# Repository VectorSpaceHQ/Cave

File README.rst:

An open source, low-cost, Raspberry Pi powered, smart thermostat. Caves are generally cooler than nests.

Overview
=======
This program's goal is to maximize the amount of time spent in the comfort zone while minimizing the energy spent when the building is occupied.

Structure
========
This system is composed of a server, one or more thermostats, and optional nodes. Their purposes and interactions are as follows,

Server
-------
The server hosts the MySQL database and the web interface. Its purpose is to collect and analyze the sensor data from the thermostat(s) and any additional nodes, and use that information to direct the thermostat(s). In essence, the server is smart. The server can be a dedicated computer or it can run on the Raspberry Pi, alongside the thermostat program.

Thermostat
-------------
The thermostat measures temperature and directly interfaces with the wiring of the HVAC unit. It reports all measurements to the server and its actions are determined by the server. The thermostat is intended to be the Raspberry Pi.

Nodes
------
Nodes are optional pieces of hardware that provide additional sensor data to the MySQL database such as temperatures, humidity, and motion. Nodes might be of value in large spaces or in rooms isolated from the thermostat.

Nodes publish data using the MQTT protocol. This is done rather than modifying the MySQL database directly, simply because these nodes are small and rarely support SQL, as in the case of the ESP8266. The RPi subscribes to the MQTT channel and inserts the data it receives into the SQL database.

Installation
===========
clone the repository to the server and thermostat(s).
::
   git clone https://github.com/VectorSpaceHQ/Cave

Server
-------
Install mysql server on the server.
::
   sudo apt-get install mysql-server

Install supporting packages.
::
   sudo apt-get install python3-dev python3-pip python3-setuptools libmysqlclient-dev python3-mysql

Generate the initial MySQL database manually, then run ./src/database.py to create the tables
::
   mysql
   CREATE DATABASE hvac;
   quit
   ./src/database.py

You can confirm that the hvac database was added to your mysql server, by loging in at http://localhost/phpmyadmin/

Install required python packages.
::
   sudo pip3 install -r ./src/requirements.txt

Install Mosquitto on the server for MQTT brokering.
::
   sudo apt-get install mosquitto

Modify server/token.txt and server/server.conf files with appropriate values based on your wiring and preferences.

Thermostat
-----------
Install required python packages.
::
   sudo pip3 install -r ./thermostat/requirements.txt

Modify thermostat/token.txt and thermostat/thermostat.conf files with appropriate values based on your wiring and preferences.

Enable SPI and 1-Wire.
::
   sudo raspi-config
> Advanced Options > Enable SPI and 1-Wire

Services
copy cave_server.service to /etc/systemd/system/ on the server
copy cave_thermostat.service to /etc/systemd/system/ on the thermostat (RPi)

enable both of these services on their respective machines using
sudo systemctl enable cave_server.service
sudo systemctl enable cave_thermostat.service

Usage
=====
On the server,
::
   ./server/server.py start

On the RPi thermostat run,
::
   ./thermostat/thermostat.py start

MySQL database
=============
The database contains four tables.

ModuleInfo
-----------
This table contains an entry for each module (thermostat or node) connected to the system. It includes a unique ID, a description of the module's location, a firmware version, and boolean values to represent the presence of temperature, humidity, light, and motion sensors.

SensorData
-------------
This table logs all of the sensor readings, including the thermostat(s).

readingID, time, moduleID, location, temperature, humidity, light, sound, motion

ThermostatLog
-----------------
This table logs only the thermostat readings.

timeStamp, mode, moduleID, MinTemp, MaxTemp, actualTemp, coolOn, heatOn, fanOn, auxOn

ThermostatSet
----------------
This table provides the current directive for the thermostat(s). The server writes to this table and the thermostat reads from it.

timeStamp, moduleID, targetTemp, targetMode, expiryTime, entryNo

SystemLog
-----------
This table logs the state of the entire system.
timeStamp, Tthermostat, Toutside, Ttarget, Poccupancy

Testing
======
This software can be tested entirely on a single Raspberry Pi. Install the sample database found in /test, then run both the server.py and thermostat.py programs.
::
    mysql -uroot -p hvac < ./test/hvac_data.txt

    python3 -m unittest discover

Hardware
=======
Below is a wiring diagram for a Raspberry Pi zero with a temperature sensor, PIR sensor, and 4 channel relay.

.. image:: ext/thermostat_schematic_bb.png
           :align: center

** Standard thermostat pins
*** Honeywell TH6320U2008
pin spacing of 5mm (https://www.mouser.com/ProductDetail/845-30.359), 1.3mm diameter. two 8 pin columns separated by 44.4mm (1.75in)
*** Honeywell TH5320U1001
pin spacing of 5mm (https://www.mouser.com/ProductDetail/845-30.359), 1.3mm diameter. One 9 pin column.

HVAC 101
=======
The following HVAC information is coppied directly from, https://github.com/Willseph/RaspberryPiThermostat

HVAC 101

HVAC (heating, ventilating, and air conditioning) can be implemented in different ways within a house or apartment, and varies for different countries based on the wiring and such. I'm not an expert in HVAC systems, I pretty much just learned enough to get by for this project, but here's a pretty useful guide: https://lrak.net/wiki/Thermostat_signals_and_wiring.html

My particular apartment uses a heat pump, which uses the very same compressor action for the air conditioner. The only difference is the air flow. This makes it possible to, in my case, use four wires from the HVAC panel behind the original thermostat for this project:

R (Red): This is the "common" wire, meaning that a circuit is completed when any of the other wires are connected to this one, hence the relay module.
G (Green): This is the signal for the fan, which becomes activated when connected to R.
Y (Yellow): This is the signal for the compressor. By default, the air flow is set to blow heat into the apartment.
O (Orange): This is the signal to reverse the air flow from the compressor. With Y and O both active, the flow changes to blow cool air into the apartment.
I broke this down to a pretty simple formula while I started writing the software for the controller:

R + G = Fan
R + G + Y = Heater
R + G + Y + O = Air conditioner

It's also very important to note that the wires coming out of my HVAC use a low voltage at 24V, not mains power. With a relay module completing the circuits, it should still work with mains electricity, but it is very dangerous and you should NOT mess with mains power unless you know exactly what you're doing! An accident involving high voltage and current can very easily kill you.

If your home HVAC does not use a compressor heat pump or for another reason you cannot use the same setup I'm using, you will have to do some research and potentially adjust the hvaccontroller.py script accordingly.

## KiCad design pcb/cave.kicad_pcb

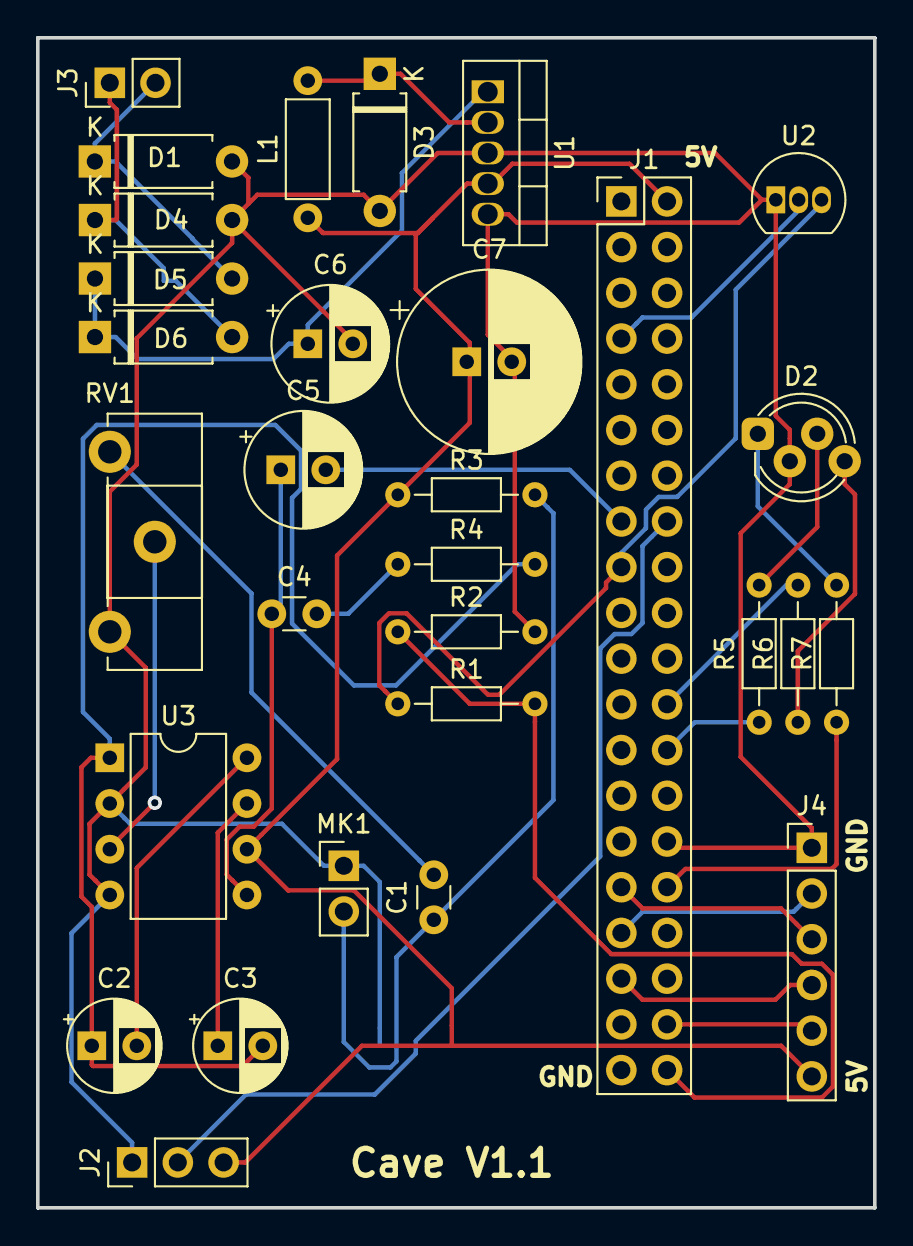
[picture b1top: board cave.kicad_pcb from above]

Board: 2 copper layers, 46.5 x 65.0 mm, 30 parts (0 on the bottom side), 29 nets.

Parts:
C1: 0.1uF; C_Disc_D3.0mm_W1.6mm_P2.50mm
C2, C3: 10uF; CP_Radial_D5.0mm_P2.50mm
C4: 0.047uF; C_Disc_D3.0mm_W1.6mm_P2.50mm
C5, C6: 100uF; CP_Radial_D6.3mm_P2.50mm
C7: 1000uF; CP_Radial_D10.0mm_P2.50mm
D1, D4, D5, D6: D_Small; D_A-405_P7.62mm_Horizontal
D2: LED_RCBG; LED_D5.0mm-4_RGB_Staggered_Pins
D3: D_Schottky; D_A-405_P7.62mm_Horizontal
J1: Raspberry_Pi_2_3; PinHeader_2x20_P2.54mm_Vertical
J2: PIRsensor; PinHeader_1x03_P2.54mm_Vertical
J3: PWR; PinHeader_1x02_P2.54mm_Vertical
J4: RelayOutput; PinHeader_1x06_P2.54mm_Vertical
L1: 100uH; L_Axial_L5.3mm_D2.2mm_P7.62mm_Horizontal_Vishay_IM-1
MK1: Microphone; PinHeader_1x02_P2.54mm_Vertical
R1: R_PHOTO; R_Axial_DIN0204_L3.6mm_D1.6mm_P7.62mm_Horizontal
R2: 10K; R_Axial_DIN0204_L3.6mm_D1.6mm_P7.62mm_Horizontal
R3: 1K; R_Axial_DIN0204_L3.6mm_D1.6mm_P7.62mm_Horizontal
R4: 10; R_Axial_DIN0204_L3.6mm_D1.6mm_P7.62mm_Horizontal
R5, R6, R7: 220; R_Axial_DIN0204_L3.6mm_D1.6mm_P7.62mm_Horizontal
RV1: 10K; Potentiometer_ACP_CA14-H2,5_Horizontal
U1: LM2576S-5; TO-220-5_Vertical
U2: DS18B20; TO-92_Inline
U3: LM386; DIP-8_W7.62mm

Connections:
+3V3: J1.17, R1.1, U2.3
+5V: C7.1, J1.2, J2.3, J4.6, L1.1, R3.1, U1.4, U3.6
+24V: D1.1, D5.2, J3.2
-24V: D4.1, D6.2, J3.1
/MicInput: C5.2, J1.15
/PIR: J1.16, J2.2
GND: C6.2, C7.2, D1.2, D2.2, D3.2, D4.2, J1.30, J2.1, J4.1, MK1.1, R2.2, RV1.3, U1.3, U1.5, U2.1, U3.2, U3.4
unnamed: C1.1, MK1.2, R3.2
unnamed: C1.2, RV1.1
unnamed: C2.1, C3.2, R4.2, U3.1
unnamed: C2.2, U3.8
unnamed: C3.1, U3.7
unnamed: C4.1, C5.1, U3.5
unnamed: C4.2, R4.1
unnamed: C6.1, D5.1, D6.1, U1.1
unnamed: D2.1, R7.2
unnamed: D2.3, R5.2
unnamed: D2.4, R6.1
unnamed: D3.1, L1.2, U1.2
unnamed: J1.7, U2.2
unnamed: J1.24, R6.2
unnamed: J1.26, R5.1
unnamed: J1.31, J4.3
unnamed: J1.32, R7.1
unnamed: J1.33, J4.2
unnamed: J1.35, J4.4
unnamed: J1.38, J4.5
unnamed: J1.40, R1.2, R2.1
unnamed: RV1.2, U3.3

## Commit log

2017-08-14 Initial commit. Nonworking state
2017-08-14 Removed developing feature
2017-08-14 corrected config file name
2017-08-14 Added config files. Still missing credentials
2017-08-14 py2to3
2017-08-14 added more sql detail to readme
2017-08-14 trying to figure out ReST
2017-08-15 expanded pyowm. Corrected logic in main loop
2017-08-15 Added occupancy check
2017-08-15 assume unoccupied before checking data
2017-08-15 Limit the sensor data query to last 50 entries
2017-08-15 fixed sorting of sensor data query
2017-08-15 some work on occupancy prediction. Still work to do
2017-08-15 py2to3 on thermostat code
2017-08-15 rename main files
2017-08-15 logging added to thermostat.py
2017-08-15 cleaning up thermostat.py
2017-08-18 minor changes
2017-08-25 Installed package on pi. updated documentation on installation and usage
2017-08-25 Updated thermostat.conf to reflect my test setup
2017-08-25 Added thermostat token file
2017-08-25 adding initialization functions to populate DB
2017-08-26 readme updates
2017-08-26 initialization functions working
2017-08-26 removed unused tables from sql schema
2017-08-26 cleanup of .sql inital database
2017-08-26 removed fan actuation from idle mode. Needs to be smarter
2017-08-26 added weather back in. Fixed sort order of sensor data
2017-08-27 changed comfort zone for easier testing
2017-08-27 idle was missing when outside temp is in comfort zone
2017-08-27 Added motion detection support
2017-08-27 Cleaned up getTemp function. Removed database communication
2017-08-28 began heat rate calculation
2017-08-29 sloppy but working implementation of an esp node
2017-08-29 began adding mqtt to server
2017-08-29 moved todo items into TODO file
2017-08-29 updates to TODO list
2017-08-29 added code support to .rst
2017-08-29 testing code support
2017-08-29 starting to understand rst syntax
2017-08-29 rst cleanup
2017-08-29 Reorg installation instructions
2017-08-29 Reorg rst
2017-08-29 Removed warranty statement from README since license covers it better
2017-08-30 Fix server install instructions
2017-08-30 Add python3-pip to the supporting packages
2017-08-30 Add python3-setuptools to the supporting packages
2017-08-30 added ping.lua to send data via GET request
2017-08-30 Add test data
2017-08-30 beginning of an error handler for the thermostat
2017-08-31 Added check_temp func to error.py. Removed Nooganeer's routes.py
2017-09-02 Initial module testing.
2017-09-02 Fixed syntax error.
2017-09-02 Fixed another syntax error.
2017-09-02 Minor testing changes.
2017-09-05 initial commit of wiring schematic
2017-09-05 Remove TODO file. Switched to github's issues
2017-09-05 added some pseudocode for email notification
2017-09-05 incorporating use of error checking
2017-09-05 Changed sensordata entry from 'occupied' to 'motion'. Sensor shouldn't be smart enough to determine if space is occupied. It detects motion. Let the server determine whether the space is occupied bas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
2017-09-05 added analysis.py file
2017-09-11 minor changes to get code running
2017-09-11 commented some weather code to get things running
2017-09-11 RGBled working
2017-09-22 Refactored server.py, moving logic from the run function into separate functions. Hopefully making code more readable.
2017-09-22 more refactoring. Moved setting of ThermostatSet table into its own function
2017-09-22 reorganizing the way occupancy is tracked
2017-09-22 Further refactoring. Moved get_sensors inside of determine_occupancy.
2017-09-22 fixed target_temp not being defined
2017-09-26 minor change to readme and commenting plot.py
2017-09-26 Added test_IO.py
2017-11-11 renamed thermostat to cave
2017-11-12 unittest imports are finally working
2017-11-12 Added init file to server package
2017-11-12 almost forgot init files for thermostat and tests
2017-11-12 unit tests are far from ideal, but at least they're doing something.
2017-11-12 removed context file
2017-11-12 readme desc update
2017-11-12 removed test daemon option
2017-11-12 Added offset support
2018-08-11 minor comments added after reviewing code again
2018-08-13 Added new table for data logging
2018-08-13 Added plotting tool
2018-08-13 added sample module to database-schema.sql to get people started
2018-08-13 added exception message to server.py
2018-08-13 added probability of occupancy method
2018-08-13 legend placement typo
2018-08-17 added sytemd service and status LED to thermostat
2018-08-17 fixed idle pause time from debug time to actual time
2018-08-18 target temp set more frequently now
2018-08-18 Expanded on plotting program in tools
2018-08-18 didn't finish merging
2018-08-19 major cleanup of plots
2018-08-20 moving away from config file on thermostat. No need for user to modify pin numbers so readily
2018-08-21 fixed bug in creating SystemLog. Changed targetTemp to float in SQL
2018-09-03 beginning complete rewrite of thermostat code
2018-09-05 continued rewrite of thermostat code
2018-09-05 added update to database
2018-09-09 work on analysis
2018-09-09 fixed local variable bugs in hvac
2018-09-09 fixed bug in fallback_mode logic
2018-09-09 added logging
2018-09-09 ready for testing
2018-09-09 added dname to database
2018-09-09 some local emergency changes
2018-09-09 beginning to add fysom
2018-09-09 implemented fysom in hvac
2018-09-09 minor fix to hvac get_state
2018-09-09 Added callbacks to hvac state machine
2018-09-09 added hvac as subclass of thermostat
2018-09-09 begin updating database
2018-09-16 starting to move to peewee
2018-09-16 fixed hvac set_state. pins weren't set as output
2018-09-16 removed get_state. Not possible because it unsets the gpio pins
2018-10-31 continued porting to peewee
2018-10-31 exception handle failed mysql connection
2018-11-06 add get_sensor_data func
2018-11-06 started over on server code server2.py
2018-11-09 Major rework of server currently in server2.py
2018-11-09 major changes to thermostat stored in thermostat2.py
2018-11-09 fixed list order number of peewee select
2018-11-09 rename files
2018-11-09 need to add database initialization
2018-11-09 database now adds initial row to each table if empty
2018-11-11 implemented expiration time in smart mode
2018-11-11 set default hysteresis values
2018-11-11 started adding weather forecast
2018-11-11 fixed bug in server.py getting temperature
2018-11-12 added future occupancy prediction. Come back to it when there's more data in the database
2018-11-12 trying to find a useful light value
2018-11-12 added temperature forecasting
2018-11-15 added config.cfg
2018-11-30 Added services and description to readme for installation
2018-11-30 added config parsing to thermostat
2018-11-30 fixed errors in cave_thermostat.service and config parsing
2018-12-06 converted post_process.py to use peewee. Also got heat rate plot working
2019-01-11 significan speedup using get instead of select
2019-01-11 implemented module based temp offset on the server
2019-02-05 Added simple radiative heat term
2019-03-21 Add pcb files
2019-04-02 speed up heartbeat
2019-04-16 started install script
2019-04-16 Added basic tests for the PCB
2019-11-15 fixed rectifier layout and PIR position
2019-11-15 added more labels to pcb
2019-11-15 confirmed led_test.py works
2019-11-15 misnamed photoresistor test
2021-04-11 created custom footprint for 5mm pins and added to schematic
2021-06-10 changes that I don't remember
2021-06-28 updated test files
2021-06-28 fixed photoresistor test pin number
2022-06-16 attempt to address bug where relays will remain in current position when software crashes. Should transition to idle state
